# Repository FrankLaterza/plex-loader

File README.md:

# Plex Loader
A PCB designed to route traffic for flashing many devices with one central programmer.

BOM (per unit) 💣
| Parts | QT | Description | Link |
|---|---|---|---|
| TMUX1208 | 3 | Bidirectional Multiplexer | [link](https://digikey.com/en/products/detail/texas-instruments/TMUX1208PWR/9746210) |
dsPIC33f | 1 | An extra PIC for testing | [link](https://www.digikey.com/en/products/detail/microchip-technology/DSPIC33FJ128GP204-E-PT/1635665) |
| MOSFET PNP | 1 | Used as pain power switch | [link](https://www.digikey.com/en/products/detail/vishay-siliconix/sq3457ev-t1-ge3/7566744) |
| 0.1uf Cap | 5 | Decoupling cap used for Mux and Pic | [link](https://www.digikey.com/en/products/detail/murata-electronics/GRM155R71C104KA88J/2610892) |
| 10uf Cap | 1 | Decoupling cap on Pic | [link](https://www.digikey.com/en/products/detail/yageo/CC0603KRX5R6BB106/5195191) |
| 10k res | 5 | General pull up | [link](https://www.digikey.com/en/products/detail/yageo/RC0603JR-0710KL/726700) |
| 1k res | 9 | Pull up and led | [link](https://www.digikey.com/en/products/detail/yageo/RC0603JR-0710KL/726700https://www.digikey.com/en/products/detail/yageo/RC0402JR-071KL/726408) |
| 100 res | 3 | Used in on MCLR on pic | [link](https://www.digikey.com/en/products/detail/yageo/RC0603FR-07100RL/726888) |
| 50 res | 2 | Used in on PGC and PGD on pic | [link](https://www.digikey.com/en/products/detail/yageo/RT0603BRE0750RL/5928059) |
| DF13-5P-1.25DS | 6 | Female conn used for program out | [link](https://www.digikey.com/en/products/detail/hirose-electric-co-ltd/DF13-5P-1-25DS-25/15997289) |
| DF13-5S-1.25C | 6 | Male conn for harness | [link](https://www.digikey.com/en/products/detail/hirose-electric-co-ltd/DF13-5S-1-25C/241752) |
| H4BXG-10112-R6 | 6 | Red wire 12"| [link](https://www.digikey.com/en/products/detail/hirose-electric-co-ltd/H4BXG-10112-R6/426070) |
| H4BBG-10112-G6 | 6 | Green wire 12" | [link](https://www.digikey.com/en/products/detail/hirose-electric-co-ltd/H4BBG-10112-G6/425566) |
| H4BBG-10112-L6 | 6 | Blue wire 12" | [link](https://www.digikey.com/en/products/detail/hirose-electric-co-ltd/H4BBG-10112-L6/425574) |
| H4BBG-10112-W6 | 6 | White wire 12"| [link](https://www.digikey.com/en/products/detail/hirose-electric-co-ltd/H4BBG-10112-W6/425614) |
| H4BBG-10112-B6 | 6 | Black wire 12"| [link](https://www.digikey.com/en/products/detail/hirose-electric-co-ltd/H4BBG-10112-B6/425558) |
| LED | 6 | Green LED for prog status | [link](https://www.digikey.com/en/products/detail/ams-osram-usa-inc/LG-R971-KN-1-0-20-R18/1227925) |
| LED | 1 | RED LED for POWER | [link](https://www.digikey.com/en/products/detail/w%C3%BCrth-elektronik/150080AS75000/11479384https://www.digikey.com/en/products/detail/w%C3%BCrth-elektronik/150080RS75000/4489918) |
| LED | 2 | Yellow LED for status | [link](https://www.digikey.com/en/products/detail/w%C3%BCrth-elektronik/150080YS75000/4489927) |
| 40-Pin Header | 1 | 20x2 pin GPIO connector designed to fit on top of the pi carrier | [link](https://www.amazon.com/2-54mm-Pitch-Female-Double-Header/dp/B083RYV9J1/ref=sr_1_5?crid=23T94ULNM1VGI&dib=eyJ2IjoiMSJ9.IZekvpBp0XXaz2v75rS4v5AAaBUo75aGOuvNzmgG0wnsSkzaQmTVWPlxJ6VvfE0f56EzXmtxPTVq_Bp05KU1vZw4qibp6W7BiLWmouShe2begYuwmQ36428Fkl8EqqnX4ZzDv6lCg2FDvj7mJGDzhcS9a4t1R-dsujDnuwS_XeSOxbsKj_jdD2DRuF0Do_GieX-ZABRTo5XiOjrZYZSxqJuPLxnLQbdPUKYzYtLkY-A.2vNHihG3SQbyL_2sp_jhnvoGpGV7xwEzqs0ZmllS3qk&dib_tag=se&keywords=2.54mm+header+long+lead+female&qid=1737236504&sprefix=2.54mm+header+long+lead+female%2Caps%2C128&sr=8-5) |
| 10-Pin Header| 1 | 2x5 used for cm4 configs | [link](https://www.amazon.com/ZYAMY-2-54mm-Straight-Stackable-Connector/dp/B0778M5P1W/ref=sr_1_3?crid=23T94ULNM1VGI&dib=eyJ2IjoiMSJ9.IZekvpBp0XXaz2v75rS4v5AAaBUo75aGOuvNzmgG0wnsSkzaQmTVWPlxJ6VvfE0f56EzXmtxPTVq_Bp05KU1vZw4qibp6W7BiLWmouShe2begYuwmQ36428Fkl8EqqnX4ZzDv6lCg2FDvj7mJGDzhcS9a4t1R-dsujDnuwS_XeSOxbsKj_jdD2DRuF0Do_GieX-ZABRTo5XiOjrZYZSxqJuPLxnLQbdPUKYzYtLkY-A.2vNHihG3SQbyL_2sp_jhnvoGpGV7xwEzqs0ZmllS3qk&dib_tag=se&keywords=2.54mm+header+long+lead+female&qid=1737236504&sprefix=2.54mm+header+long+lead+female%2Caps%2C128&sr=8-3) |

Label Guide

| Components                     | Value/Part Number           |
|--------------------------------|-----------------------------|
| C1, C2, C3, C4, C5             | 0.1 µF                     |
| C6                             | 10 µF                      |
| D1, D2, D3, D4, D5, D6, D7, D8, D9 | LED                        |
| J1, J2, J3, J4, J5, J6         | DF13-5P-1.25DS             |
| J9                             | 40-Pin Header |
| J10                            | 10-Pin Header        |
| R1, R3, R5, R6, R10            | 10 kΩ                      |
| R4, R11, R12, R13, R14, R15, R16, R17, R18 | 1 kΩ                |
| R2, R9 R19                        | 100 Ω                      |
| R7, R8                     | 50 Ω                       |
| U1, U2, U3                     | TMUX1208PWR                |
| U4                             | dsPIC33f          |
| U5                             | MOSFET PNP            |

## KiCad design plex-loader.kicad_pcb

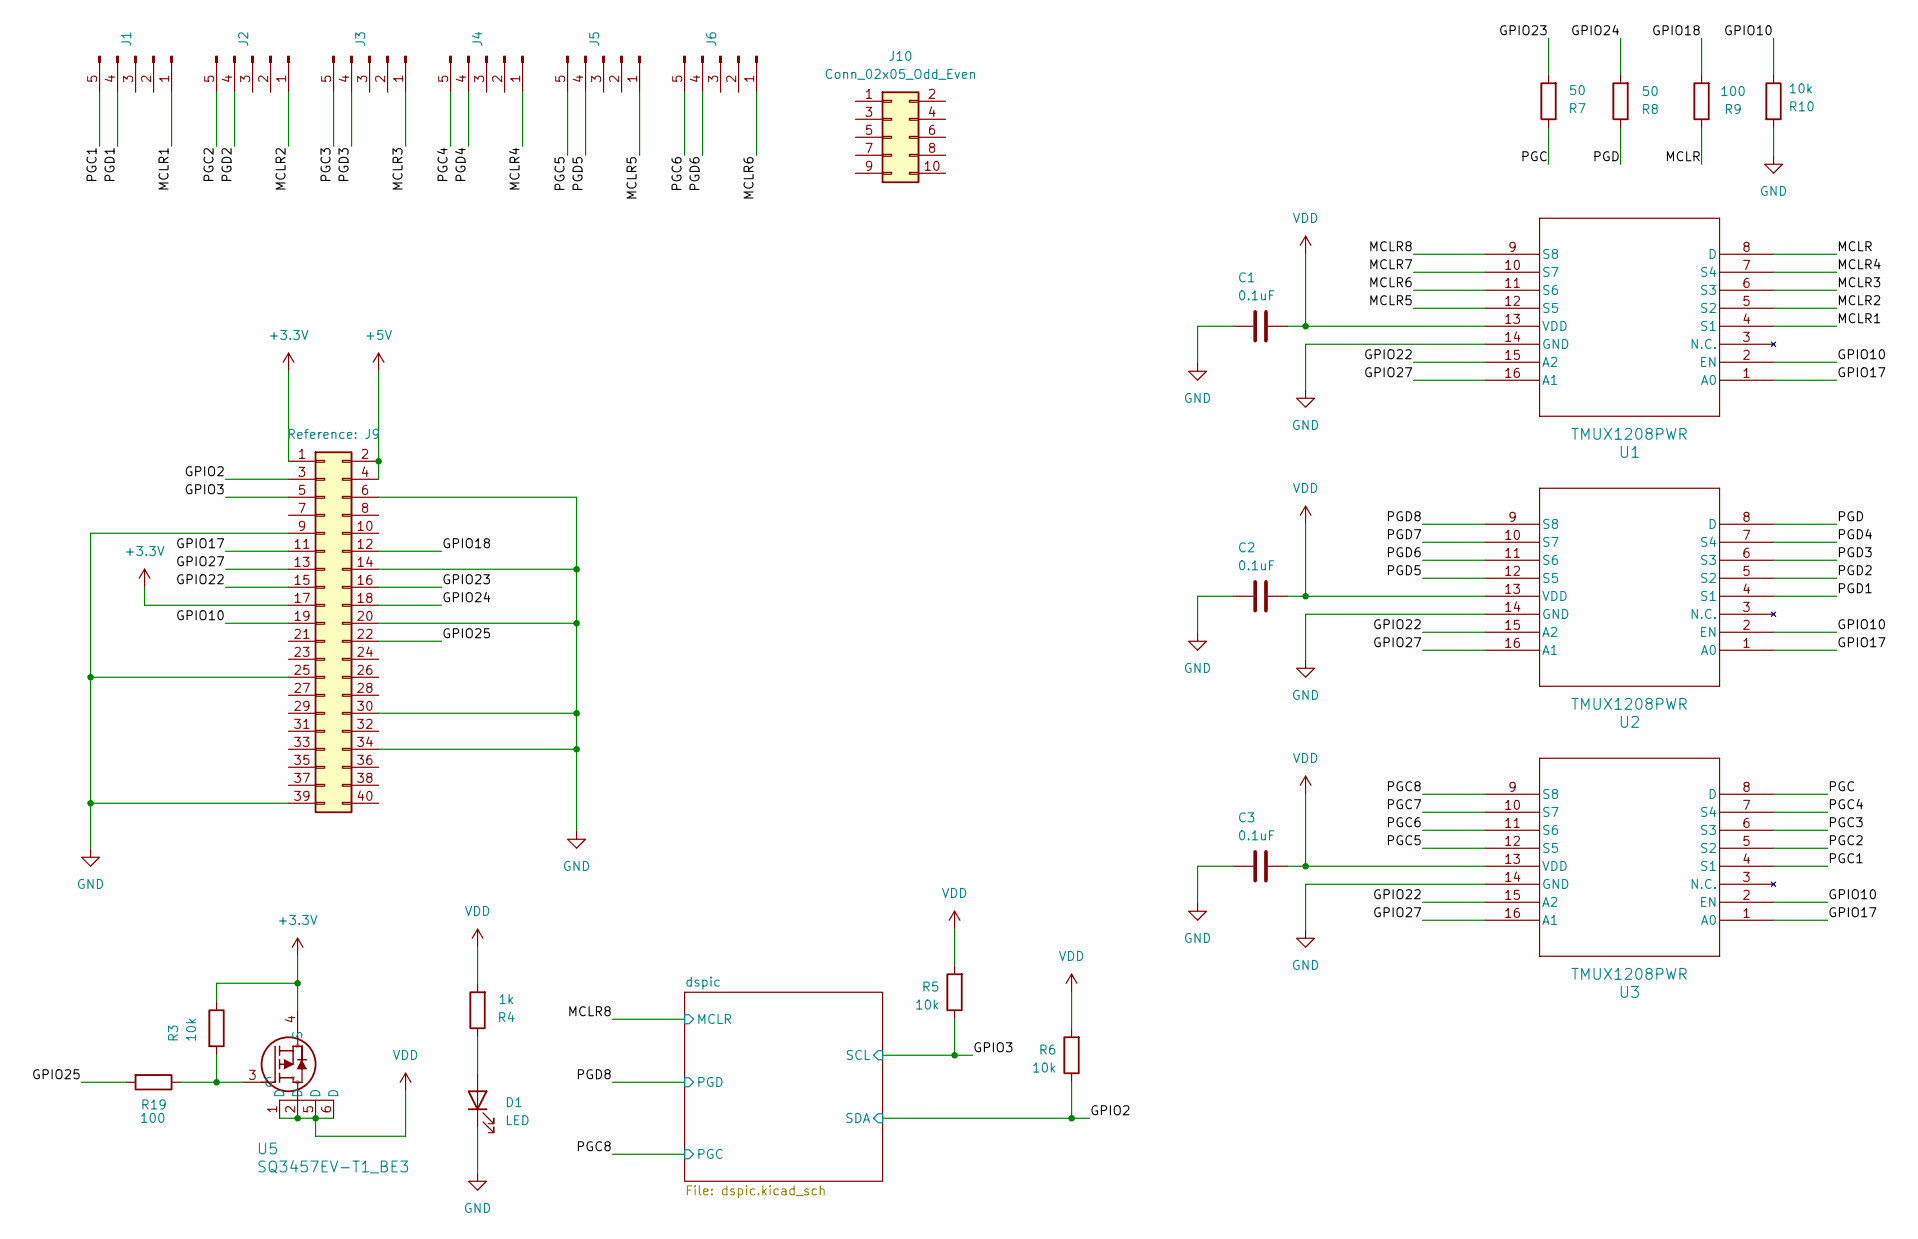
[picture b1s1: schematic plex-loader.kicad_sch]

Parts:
C1, C2, C3: 0.1uF; C_0402_1005Metric
D1: LED; LED_0805_2012Metric
J1, J2, J3, J4, J5, J6: Conn_01x05_Pin; Hirose_DF13-05P-1.25DS_1x05_P1.25mm_Horizontal
J9: Conn_02x20_Odd_Even; PinHeader_2x20_P2.54mm_Vertical
J10: Conn_02x05_Odd_Even; PinHeader_2x05_P2.54mm_Vertical
R3, R5, R6, R10: 10k; R_0603_1608Metric
R4: 1k; R_0603_1608Metric
R7, R8: 50; R_0603_1608Metric
R9, R19: 100; R_0603_1608Metric
U1, U2, U3: TMUX1208PWR; PW_16_TEX
U5: SQ3457EV-T1_BE3; TSOP_7EV-T1_BE3_VIS

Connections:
+3.3V: J9.1, J9.17, R3.1, U5.4 (S)
+5V: J9.2, J9.4
/GPIO2: J9.3, R6.1; also elsewhere on the board
/GPIO3: J9.5, R5.1; also elsewhere on the board
/GPIO10: J9.19, R10.1, U1.2 (EN), U2.2 (EN), U3.2 (EN)
/GPIO17: J9.11, U1.1 (A0), U2.1 (A0), U3.1 (A0)
/GPIO18: J9.12, R9.2
/GPIO22: J9.15, U1.15 (A2), U2.15 (A2), U3.15 (A2)
/GPIO23: J9.16, R7.2
/GPIO24: J9.18, R8.2
/GPIO25: J9.22, R19.2
/GPIO27: J9.13, U1.16 (A1), U2.16 (A1), U3.16 (A1)
/MCLR: R9.1, U1.8 (D)
/MCLR1: J1.1, U1.4 (S1)
/MCLR2: J2.1, U1.5 (S2)
/MCLR3: J3.1, U1.6 (S3)
/MCLR4: J4.1, U1.7 (S4)
/MCLR5: J5.1, U1.12 (S5)
/MCLR6: J6.1, U1.11 (S6)
/MCLR7: U1.10 (S7)
/MCLR8: U1.9 (S8); also elsewhere on the board
/PGC: R7.1, U3.8 (D)
/PGC1: J1.5, U3.4 (S1)
/PGC2: J2.5, U3.5 (S2)
/PGC3: J3.5, U3.6 (S3)
/PGC4: J4.5, U3.7 (S4)
/PGC5: J5.5, U3.12 (S5)
/PGC6: J6.5, U3.11 (S6)
/PGC7: U3.10 (S7)
/PGC8: U3.9 (S8); also elsewhere on the board
/PGD: R8.1, U2.8 (D)
/PGD1: J1.4, U2.4 (S1)
/PGD2: J2.4, U2.5 (S2)
/PGD3: J3.4, U2.6 (S3)
/PGD4: J4.4, U2.7 (S4)
/PGD5: J5.4, U2.12 (S5)
/PGD6: J6.4, U2.11 (S6)
/PGD7: U2.10 (S7)
/PGD8: U2.9 (S8); also elsewhere on the board
GND: C1.1, C2.1, C3.1, D1.1 (K), J9.6, J9.9, J9.14, J9.20, J9.25, J9.30, J9.34, J9.39, R10.2, U1.14 (GND), U2.14 (GND), U3.14 (GND); also elsewhere on the board
unnamed: D1.2 (A), R4.1
unnamed: R3.2, R19.1, U5.3 (G)
VDD: C1.2, C2.2, C3.2, R4.2, R5.2, R6.2, U1.13 (VDD), U2.13 (VDD), U3.13 (VDD), U5.1 (D), U5.2 (D), U5.5 (D), U5.6 (D); also elsewhere on the board

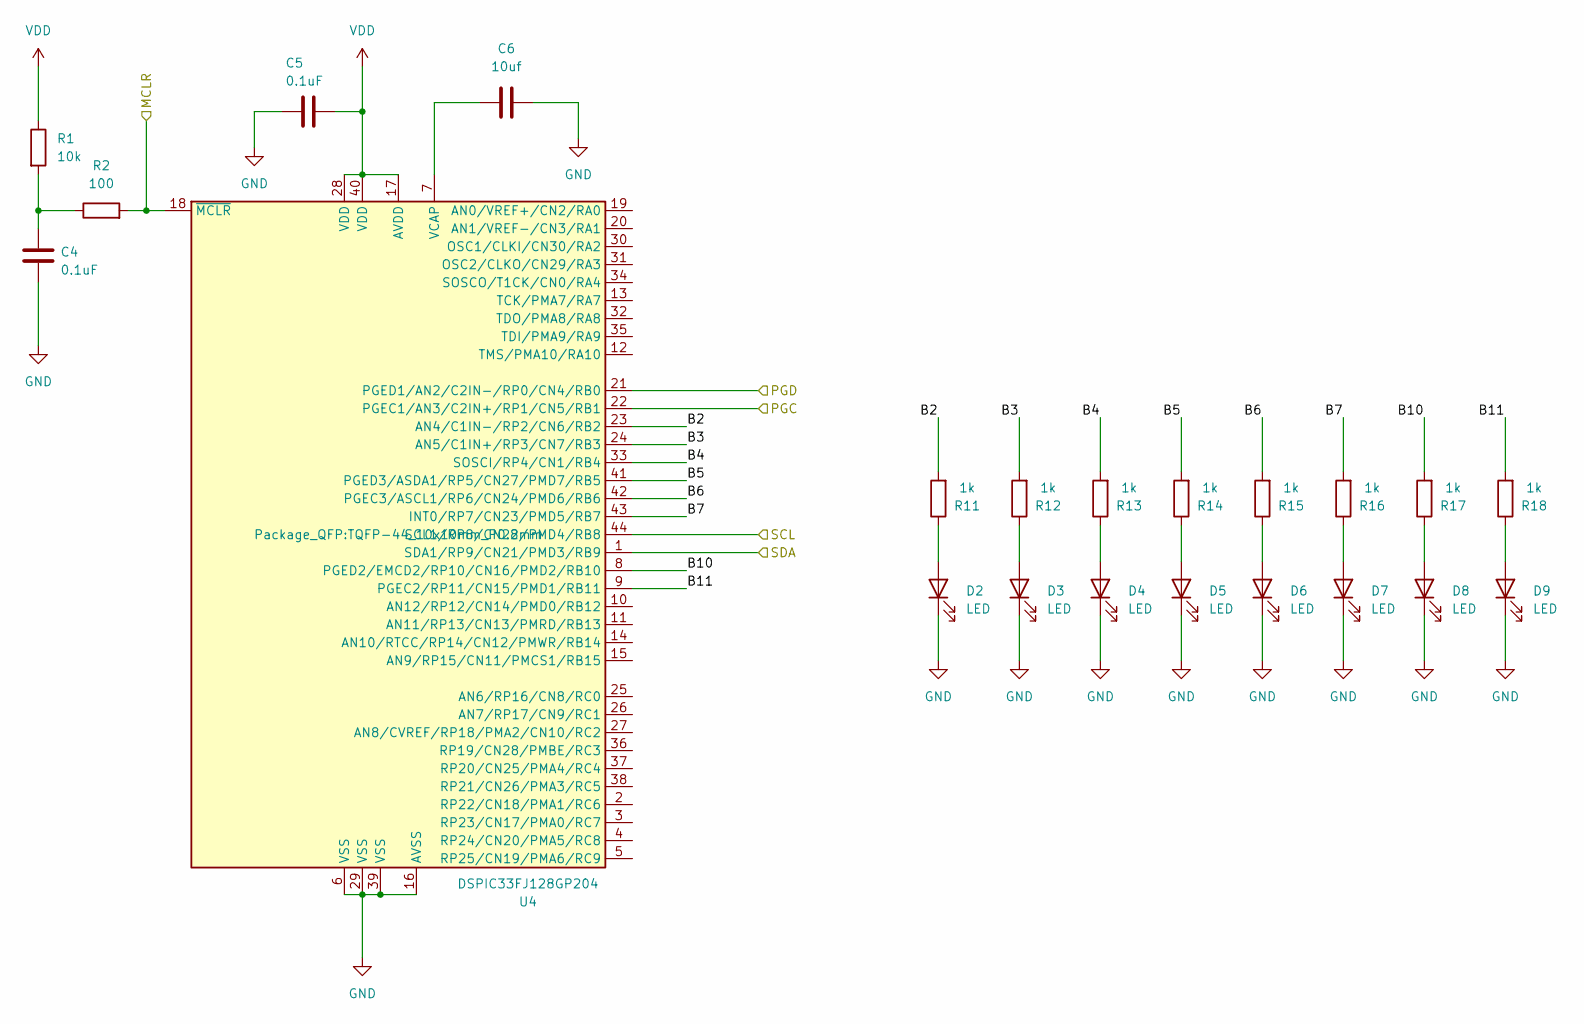
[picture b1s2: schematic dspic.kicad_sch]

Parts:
C4, C5: 0.1uF; C_0402_1005Metric
C6: 10uf; C_0603_1608Metric
D2, D3, D4, D5, D6, D7, D8, D9: LED; LED_0805_2012Metric
R1: 10k; R_0603_1608Metric
R2: 100; R_0603_1608Metric
R11, R12, R13, R14, R15, R16, R17, R18: 1k; R_0603_1608Metric
U4: DSPIC33FJ128GP204; TQFP-44_10x10mm_P0.8mm

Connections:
/GPIO2: U4.1 (SDA1/RP9/CN21/PMD3/RB9); also elsewhere on the board
/GPIO3: U4.44 (SCL1/RP8/CN22/PMD4/RB8); also elsewhere on the board
/MCLR8: R2.2, U4.18 (~MCLR); also elsewhere on the board
/PGC8: U4.22 (PGEC1/AN3/C2IN+/RP1/CN5/RB1); also elsewhere on the board
/PGD8: U4.21 (PGED1/AN2/C2IN-/RP0/CN4/RB0); also elsewhere on the board
/dspic/B2: R11.2, U4.23 (AN4/C1IN-/RP2/CN6/RB2)
/dspic/B3: R12.2, U4.24 (AN5/C1IN+/RP3/CN7/RB3)
/dspic/B4: R13.2, U4.33 (SOSCI/RP4/CN1/RB4)
/dspic/B5: R14.2, U4.41 (PGED3/ASDA1/RP5/CN27/PMD7/RB5)
/dspic/B6: R15.2, U4.42 (PGEC3/ASCL1/RP6/CN24/PMD6/RB6)
/dspic/B7: R16.2, U4.43 (INT0/RP7/CN23/PMD5/RB7)
/dspic/B10: R17.2, U4.8 (PGED2/EMCD2/RP10/CN16/PMD2/RB10)
/dspic/B11: R18.2, U4.9 (PGEC2/RP11/CN15/PMD1/RB11)
GND: C4.1, C5.1, C6.2, D2.1 (K), D3.1 (K), D4.1 (K), D5.1 (K), D6.1 (K), D7.1 (K), D8.1 (K), D9.1 (K), U4.6 (VSS), U4.16 (AVSS), U4.29 (VSS), U4.39 (VSS); also elsewhere on the board
unnamed: C4.2, R1.2, R2.1
unnamed: D2.2 (A), R11.1
unnamed: D3.2 (A), R12.1
unnamed: D4.2 (A), R13.1
unnamed: D5.2 (A), R14.1
unnamed: D6.2 (A), R15.1
unnamed: D7.2 (A), R16.1
unnamed: D8.2 (A), R17.1
unnamed: D9.2 (A), R18.1
unnamed: C6.1, U4.7 (VCAP)
VDD: C5.2, R1.1, U4.17 (AVDD), U4.28 (VDD), U4.40 (VDD); also elsewhere on the board

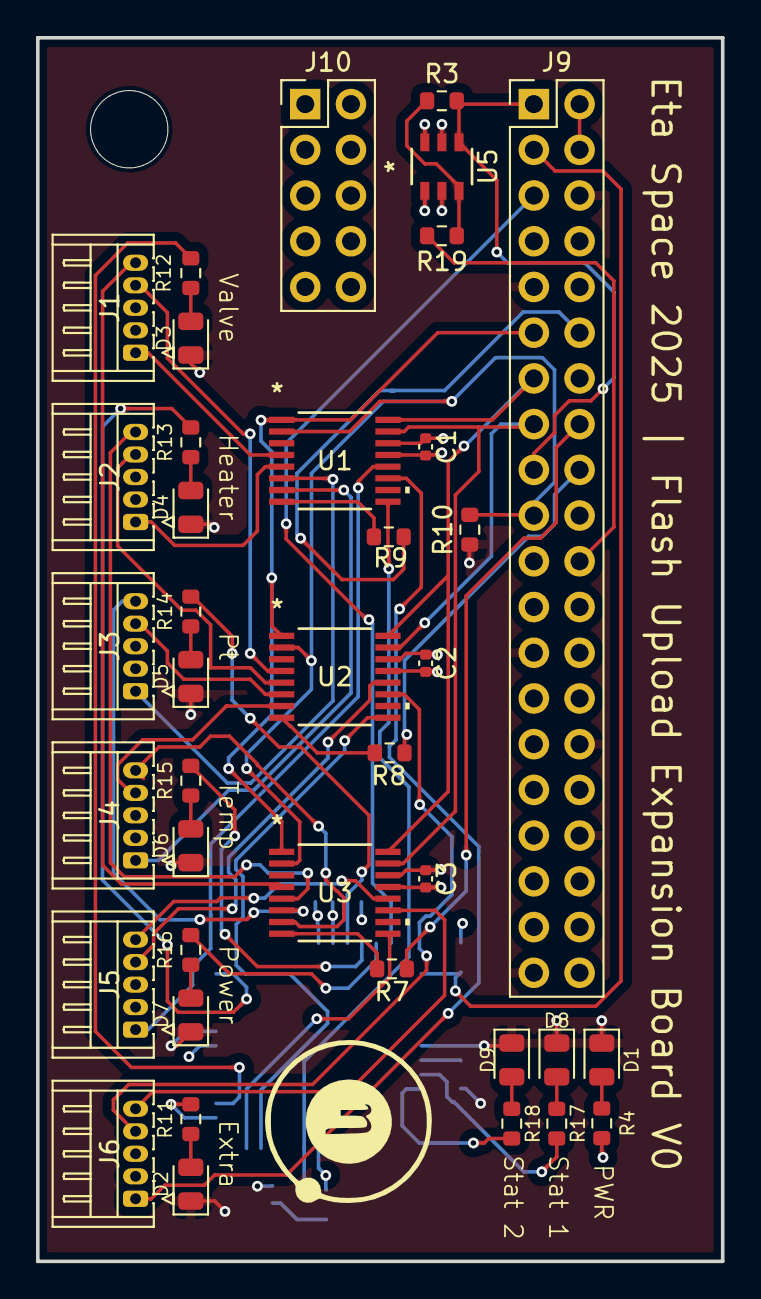
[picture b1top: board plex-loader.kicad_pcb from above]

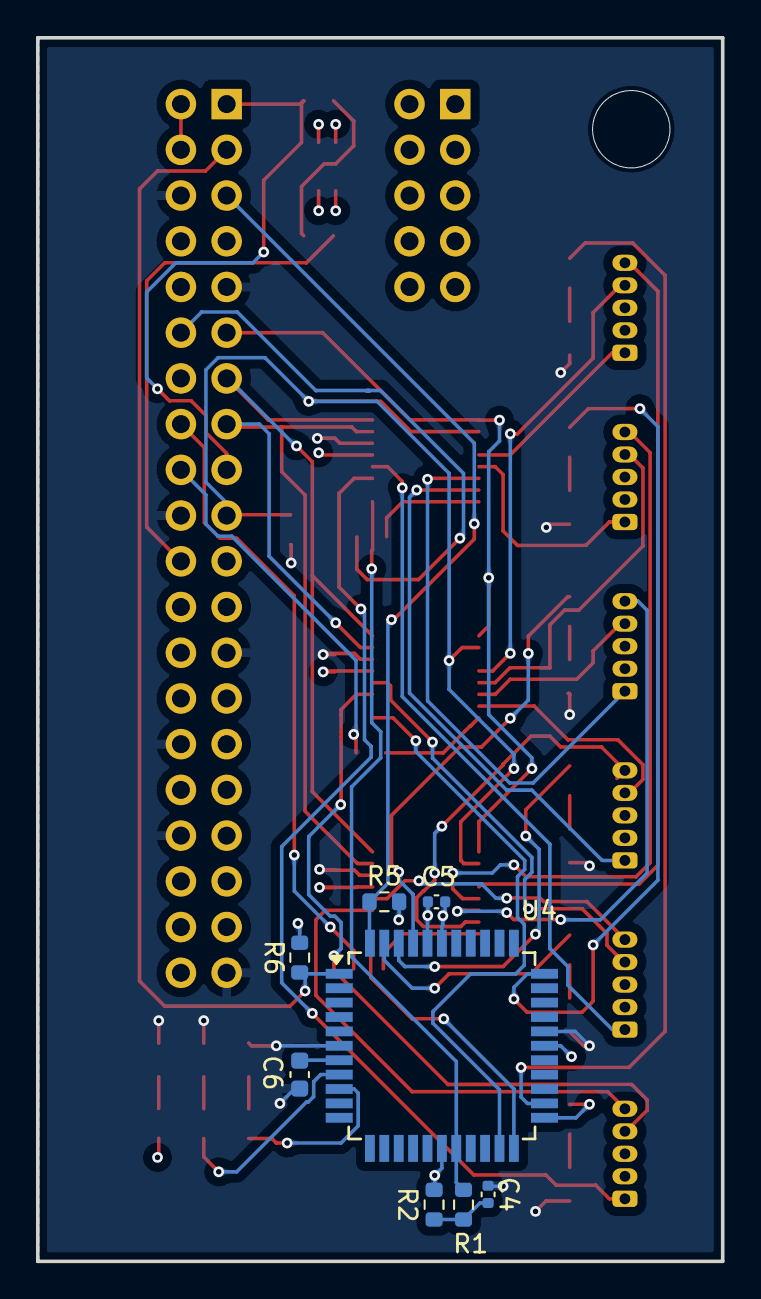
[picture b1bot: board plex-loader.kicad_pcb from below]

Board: 4 copper layers, 38.1 x 68.0 mm, 47 parts (8 on the bottom side), 58 nets.

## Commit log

2025-01-08 first
2025-01-08 second
2025-01-12 switched footprint
2025-01-15 update layers
2025-01-15 saved
2025-01-18 curtis changes
2025-01-18 route draft
2025-01-18 trace touchup
2025-01-18 fix res val
2025-01-18 removed pad via
2025-01-23 final 0v
2025-01-23 updated grbr
2025-01-23 added readme
2025-01-23 update bom
2025-01-23 fixed bom
